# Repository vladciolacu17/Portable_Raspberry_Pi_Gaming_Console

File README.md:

# Portable Raspberry Pi Gaming Console

A portable gaming console built using **Raspberry Pi**, **Python**, **Pygame**, GPIO buttons, and an analog joystick.

This project implements a complete handheld gaming system with a graphical menu and multiple playable games, including **Snake**, **Tetris**, **a Platformer**, and a **Slither-style multiplayer prototype**.

---

## Project Overview

This project explores the design and implementation of a **portable embedded gaming system** using low-cost hardware and custom software.

The console integrates:

- Raspberry Pi 4
- HDMI display
- GPIO buttons
- Analog joystick input
- Python / Pygame game engine
- Custom graphical game launcher

The system boots into a fullscreen graphical menu where the user can navigate between games and launch them directly from the console interface.

The goal of the project is to combine **embedded hardware development**, **game programming**, and **system architecture design** into a single portable device.

---

## System Architecture

The system consists of the following major components:

| Component | Role |
|----------|------|
| Raspberry Pi 4 | Main computing unit |
| HDMI Display | Game output |
| GPIO Buttons | Player input |
| Analog Joystick | Directional control |
| ADC Converter | Reads analog joystick signals |
| Power System | Portable power supply |

The Raspberry Pi runs the Python-based game framework, handles GPIO input, processes joystick signals, renders graphics, and switches between the different games.

---

## Software Architecture

The software is organized into several modules:

| Module | Description |
|--------|-------------|
| `main.py` | Main console launcher and game menu |
| `main_platformer.py` | Platformer entry point |
| `utils.py` | GPIO and joystick input handling |
| `settings.py` | Game constants and world configuration |
| `world.py` | Platformer world generation and collision logic |
| `player.py` | Player behavior and animation |
| `tile.py` | Terrain tiles |
| `trap.py` | Trap mechanics |
| `goal.py` | Goal object logic |
| `slither.py` | Slither-style game prototype |
| `support.py` | Asset loading utilities |

The main launcher initializes the display, reads the controls, shows the menu, and starts the selected game.

---

## Games Implemented

### Snake

Classic Snake implementation featuring:

- food spawning
- score tracking
- increasing speed
- joystick and button controls

### Tetris

Tetris implementation including:

- tetromino rotation
- line clearing
- score system
- responsive controls

### Platformer

The platformer game includes:

- tile-based world
- traps and hazards
- gravity and collisions
- player animations
- scrolling gameplay
- goal-based level completion

### Slither Prototype

A Slither-style multiplayer game prototype integrated into the console menu.

---

## Controls

### GPIO Button Mapping

| Function | GPIO Pin |
|----------|----------|
| Up | GPIO 26 |
| Down | GPIO 19 |
| Left | GPIO 13 |
| Right | GPIO 6 |
| Select | GPIO 5 |
| Reset | GPIO 21 |

### ADC Pins

| Signal | GPIO |
|--------|------|
| CLK | 23 |
| DO | 16 |
| DI | 20 |
| CS | 24 |

The joystick input is read through an ADC converter, allowing analog directional control.

---

## Repository Structure

```text
Portable_Raspberry_Pi_Gaming_Console/
├── README.md
├── requirements.txt
├── docs/
│   └── screenshots/
│       ├── menu.png
│       ├── snake.png
│       ├── tetris.png
│       └── platformer.png
│   └── demo/
        ├──demo_video.mp4
├── hardware/
│   
├── src/
|   |── assets/
|   |── static/
│   ├── main.py
│   ├── main_platformer.py
│   ├── settings.py
│   ├── utils.py
│   ├── world.py
│   ├── player.py
│   ├── goal.py
│   ├── trap.py
│   ├── tile.py
│   ├── slither.py
│   └── support.py

```

---

## Installation

Clone the repository:

```bash
git clone https://github.com/vladciolacu17/Portable_Raspberry_Pi_Gaming_Console.git
cd Portable_Raspberry_Pi_Gaming_Console
```

Install dependencies:

```bash
pip install -r requirements.txt
```

## Running the Project

Run the main console launcher:

```bash
python3 src/main.py
```

## Screenshots

### Snake

### Tetris

### Platformer

### Slither

---

## Demo

Watch the console running:

[Demo Video](docs/demo/DEMO.mp4)

---

## Future Improvements

Possible future improvements include:

- improved joystick calibration
- battery monitoring
- audio support
- additional games
- performance optimization for small displays

---
------------------------------------------------------------
Author
------------------------------------------------------------

Vlad-Stefan Ciolacu<br>
GitHub: https://github.com/vladciolacu17

------------------------------------------------------------
License
------------------------------------------------------------

MIT License

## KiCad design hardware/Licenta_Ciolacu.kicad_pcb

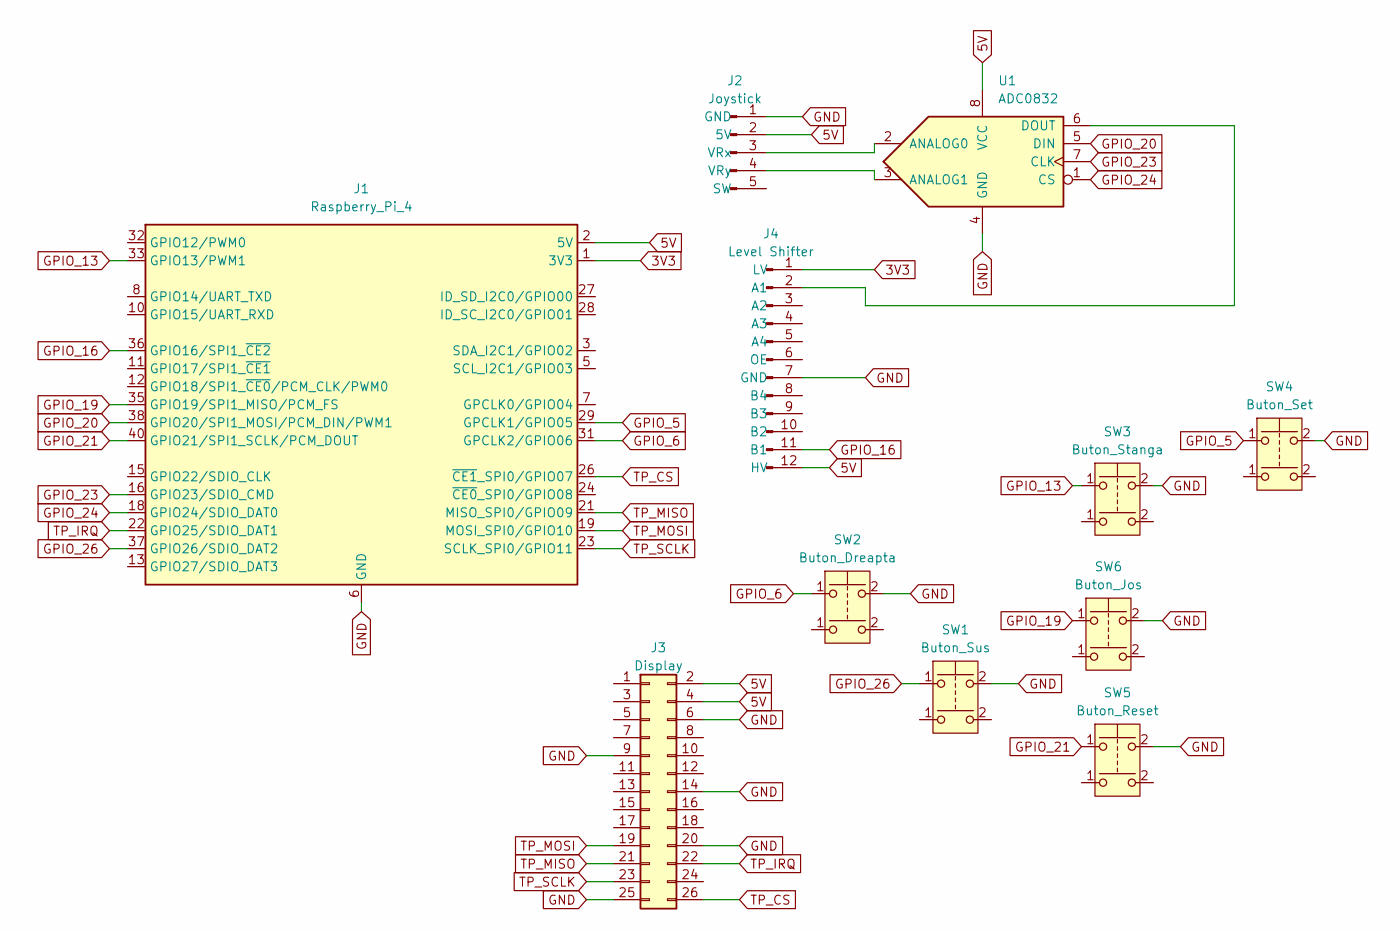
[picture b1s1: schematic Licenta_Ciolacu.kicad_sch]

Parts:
J1: Raspberry_Pi_4; RPi
J2: Joystick; PinHeader_1x05_P2.54mm_Vertical
J3: Display; MPI3508
J4: Level Shifter; DIP-12_W10.16mm
SW1: Buton_Sus; SW_PUSH-12mm
SW2: Buton_Dreapta; SW_PUSH-12mm
SW3: Buton_Stanga; SW_PUSH-12mm
SW4: Buton_Set; SW_PUSH-12mm
SW5: Buton_Reset; SW_PUSH-12mm
SW6: Buton_Jos; SW_PUSH-12mm
U1: ADC0832; DIP-8_W7.62mm

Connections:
3V3: J1.1 (3V3), J1.17 (3V3), J4.1 (LV)
5V: J1.2 (5V), J1.4 (5V), J2.2 (5V), J3.2 (Pin_26), J3.4 (4Pin_25), J4.12 (HV), U1.8 (VCC)
GND: J1.6 (GND), J1.9 (GND), J1.14 (GND), J1.20 (GND), J1.25 (GND), J1.30 (GND), J1.34 (GND), J1.39 (GND), J2.1 (GND), J3.6 (Pin_24), J3.9 (Pin_5), J3.14 (Pin_20), J3.20 (2Pin_17), J3.25 (Pin_13), J4.7 (GND), SW1.2, SW2.2, SW3.2, SW4.2, SW5.2, SW6.2, U1.4 (GND)
GPIO_5: J1.29 (GPCLK1/GPIO05), SW4.1
GPIO_6: J1.31 (GPCLK2/GPIO06), SW2.1
GPIO_13: J1.33 (GPIO13/PWM1), SW3.1
GPIO_16: J1.36 (GPIO16/SPI1_~CE2), J4.11 (B1)
GPIO_19: J1.35 (GPIO19/SPI1_MISO/PCM_FS), SW6.1
GPIO_20: J1.38 (GPIO20/SPI1_MOSI/PCM_DIN/PWM1), U1.5 (DIN)
GPIO_21: J1.40 (GPIO21/SPI1_SCLK/PCM_DOUT), SW5.1
GPIO_23: J1.16 (GPIO23/SDIO_CMD), U1.7 (CLK)
GPIO_24: J1.18 (GPIO24/SDIO_DAT0), U1.1 (CS)
GPIO_26: J1.37 (GPIO26/SDIO_DAT2), SW1.1
unnamed: J2.3 (VRx), U1.2 (ANALOG0)
unnamed: J2.4 (VRy), U1.3 (ANALOG1)
unnamed: J4.2 (A1), U1.6 (DOUT)
TP_CS: J1.26 (~CE1_SPI0/GPIO07), J3.26 (Pin_14)
TP_IRQ: J1.22 (GPIO25/SDIO_DAT1), J3.22 (Pin_16)
TP_MISO: J1.21 (MISO_SPI0/GPIO09), J3.21 (Pin_11)
TP_MOSI: J1.19 (MOSI_SPI0/GPIO10), J3.19 (Pin_10)
TP_SCLK: J1.23 (SCLK_SPI0/GPIO11), J3.23 (Pin_12)

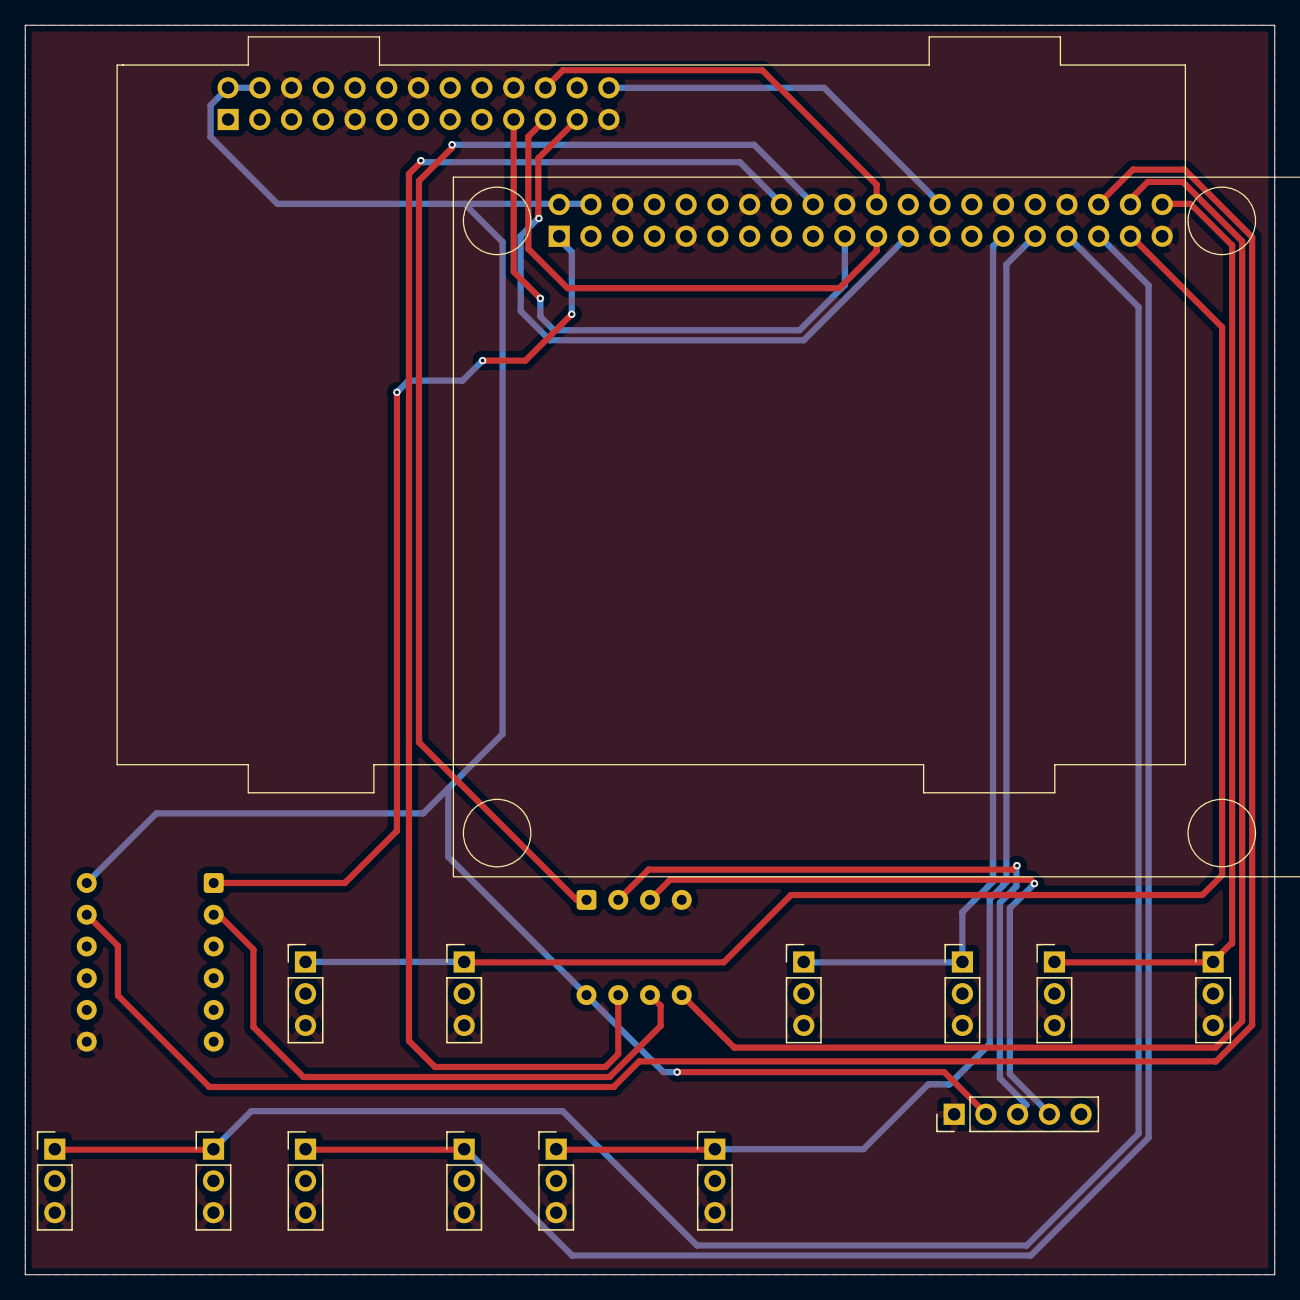
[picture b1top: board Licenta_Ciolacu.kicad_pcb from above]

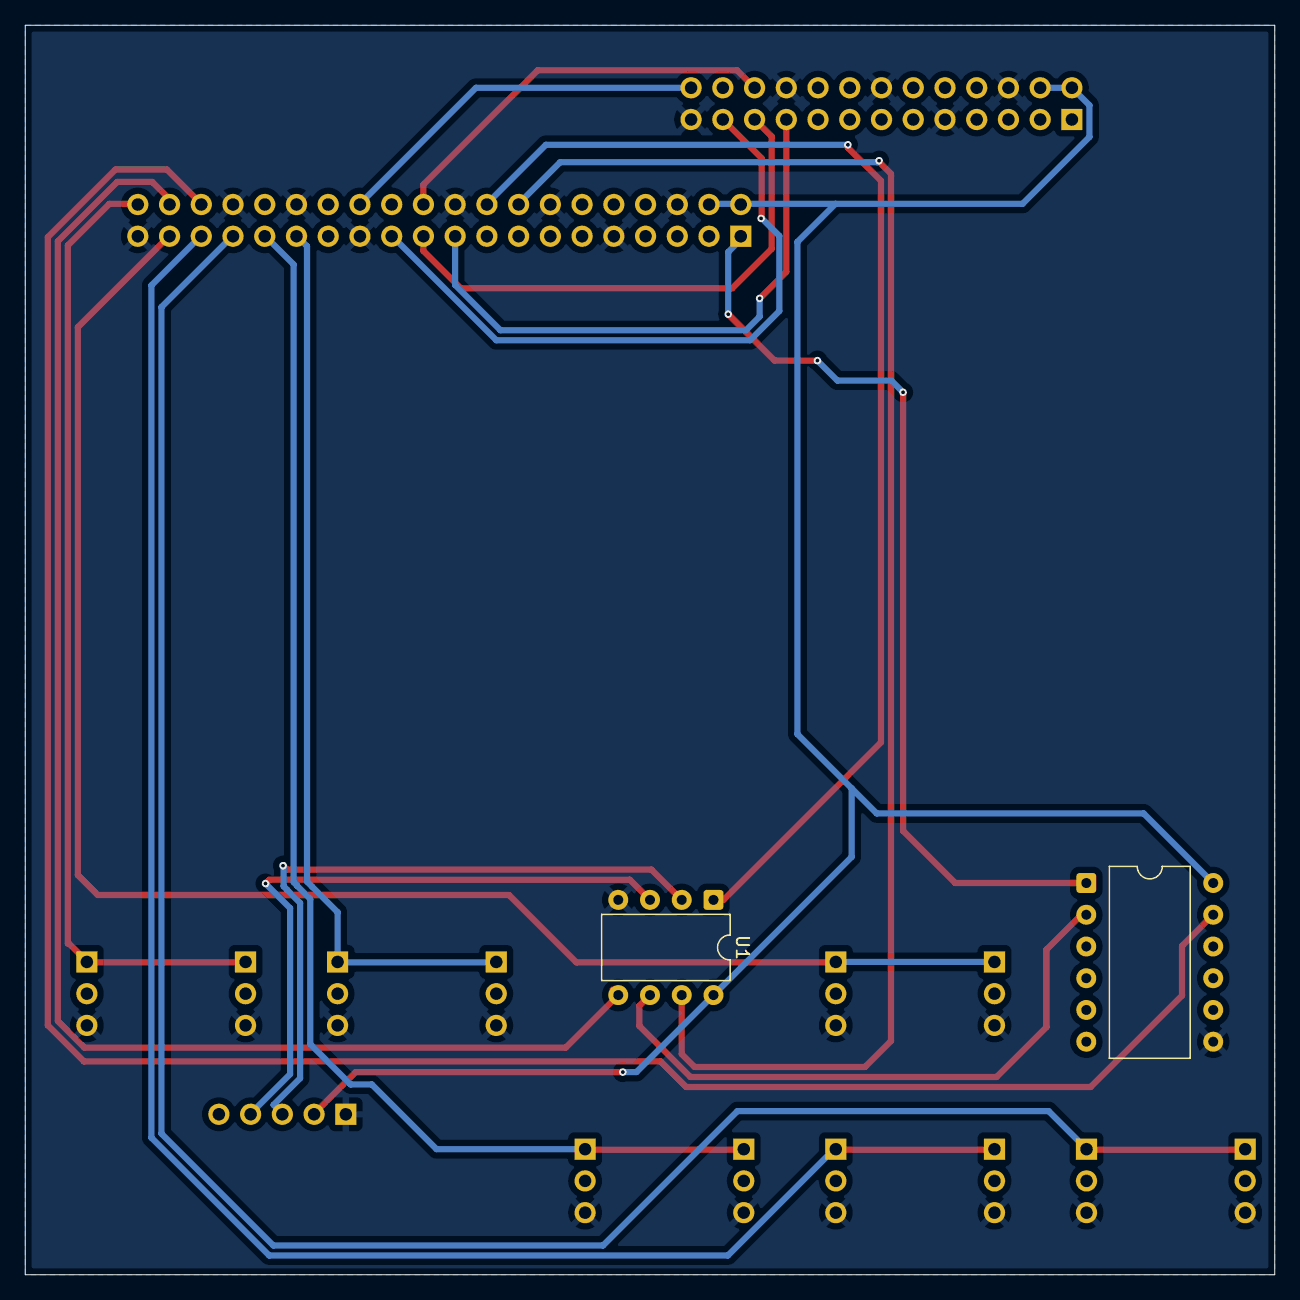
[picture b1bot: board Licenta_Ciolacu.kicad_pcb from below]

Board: 2 copper layers, 100.0 x 100.0 mm, 11 parts (2 on the bottom side), 21 nets.

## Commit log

2025-05-25 first commit is the hardest
2026-03-12 Update README with project details and features
    Added detailed project description, features, and repository structure.
2026-03-12 Add required packages for the project
2026-03-12 Redone the project structure
2026-03-12 Redone photos
2026-03-12 Change GIF format for game screenshots
2026-03-12 Add MIT License to the project
2026-03-12 Add author and license sections to README
